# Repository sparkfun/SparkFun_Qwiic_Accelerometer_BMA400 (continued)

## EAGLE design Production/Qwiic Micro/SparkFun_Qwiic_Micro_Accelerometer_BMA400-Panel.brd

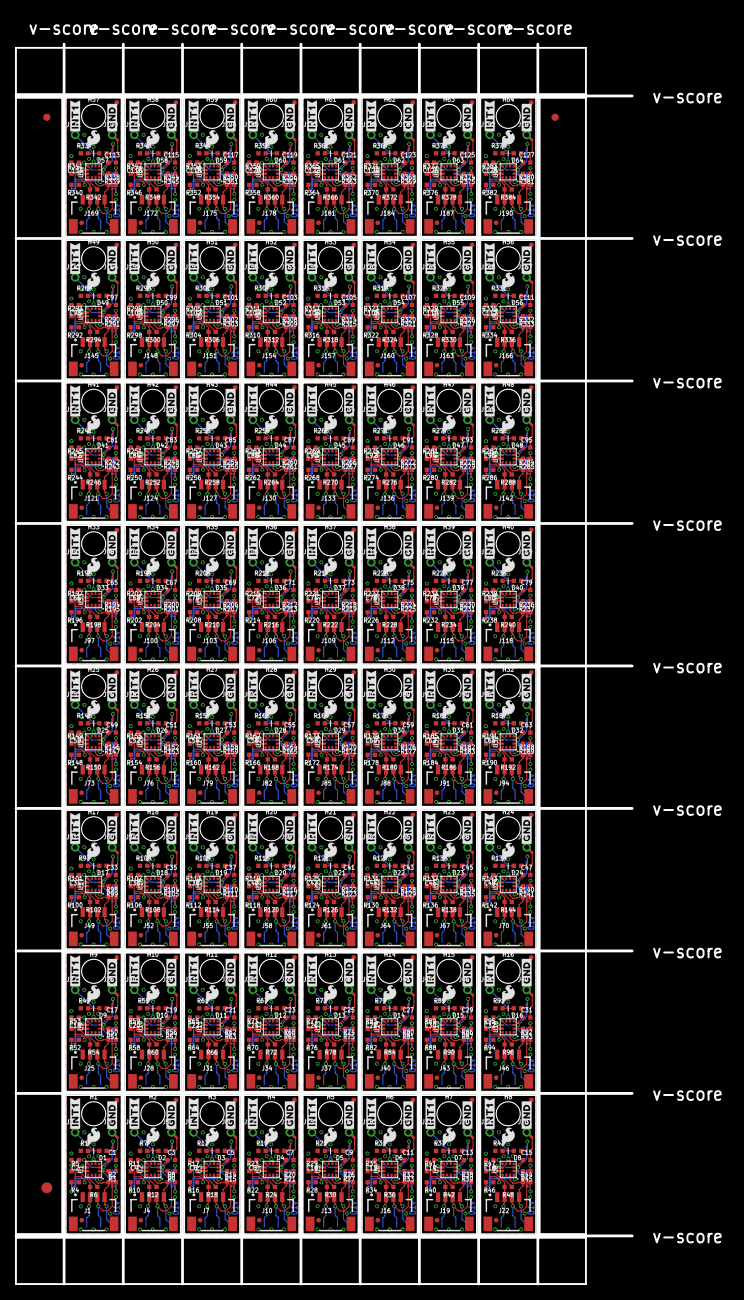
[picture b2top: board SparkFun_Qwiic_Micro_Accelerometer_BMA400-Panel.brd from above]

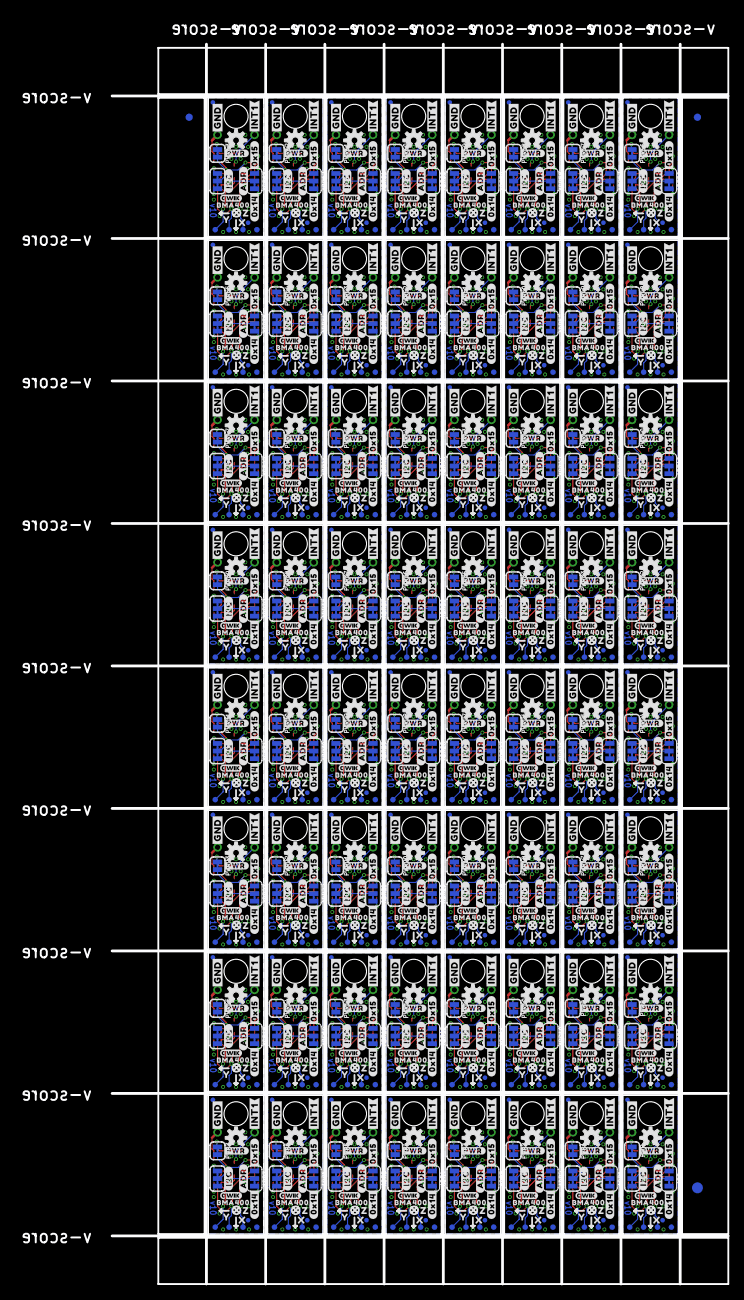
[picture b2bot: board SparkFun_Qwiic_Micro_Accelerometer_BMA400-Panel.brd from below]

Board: 2 copper layers, 84.6 x 170.2 mm, 2758 parts (1411 on the bottom side), 832 nets.

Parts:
ADR, ADR1, ADR2, ADR3, ADR4, ADR5, ADR6, ADR7, ADR8, ADR9, ADR10, ADR11, ADR12, ADR13, ADR14, ADR15, ADR16, ADR17, ADR18, ADR19, ADR20, ADR21, ADR22, ADR23, ADR24, ADR25, ADR26, ADR27, ADR28, ADR29, ADR30, ADR31, ADR32, ADR33, ADR34, ADR35, ADR36, ADR37, ADR38, ADR39, ADR40, ADR41, ADR42, ADR43, ADR44, ADR45, ADR46, ADR47, ADR48, ADR49, ADR50, ADR51, ADR52, ADR53, ADR54, ADR55, ADR56, ADR57, ADR58, ADR59, ADR60, ADR61, ADR62, ADR63: JUMPER-SMT_3_1-NC_TRACE_SILK; SMT-JUMPER_3_1-NC_TRACE_SILK
C1, C2, C3, C4, C5, C6, C7, C8, C9, C10, C11, C12, C13, C14, C15, C16, C17, C18, C19, C20, C21, C22, C23, C24, C25, C26, C27, C28, C29, C30, C31, C32, C33, C34, C35, C36, C37, C38, C39, C40, C41, C42, C43, C44, C45, C46, C47, C48, C49, C50, C51, C52, C53, C54, C55, C56, C57, C58, C59, C60, C61, C62, C63, C64, C65, C66, C67, C68, C69, C70, C71, C72, C73, C74, C75, C76, C77, C78, C79, C80, C81, C82, C83, C84, C85, C86, C87, C88, C89, C90, C91, C92, C93, C94, C95, C96, C97, C98, C99, C100, C101, C102, C103, C104, C105, C106, C107, C108, C109, C110, C111, C112, C113, C114, C115, C116, C117, C118, C119, C120, C121, C122, C123, C124, C125, C126, C127, C128: 0.1uF; 0402-TIGHT
D1, D2, D3, D4, D5, D6, D7, D8, D9, D10, D11, D12, D13, D14, D15, D16, D17, D18, D19, D20, D21, D22, D23, D24, D25, D26, D27, D28, D29, D30, D31, D32, D33, D34, D35, D36, D37, D38, D39, D40, D41, D42, D43, D44, D45, D46, D47, D48, D49, D50, D51, D52, D53, D54, D55, D56, D57, D58, D59, D60, D61, D62, D63, D64: RED; LED-0402
E$1, E$2, E$3, E$4: FIDUCIAL-1X2
E$5, E$6: FIDUCIAL-1.5X3
FD1, FD2, FD3, FD4, FD5, FD6, FD7, FD8, FD9, FD10, FD11, FD12, FD13, FD14, FD15, FD16, FD17, FD18, FD19, FD20, FD21, FD22, FD23, FD24, FD25, FD26, FD27, FD28, FD29, FD30, FD31, FD32, FD33, FD34, FD35, FD36, FD37, FD38, FD39, FD40, FD41, FD42, FD43, FD44, FD45, FD46, FD47, FD48, FD49, FD50, FD51, FD52, FD53, FD54, FD55, FD56, FD57, FD58, FD59, FD60, FD61, FD62, FD63, FD64, FD65, FD66, FD67, FD68, FD69, FD70, FD71, FD72, FD73, FD74, FD75, FD76, FD77, FD78, FD79, FD80, FD81, FD82, FD83, FD84, FD85, FD86, FD87, FD88, FD89, FD90, FD91, FD92, FD93, FD94, FD95, FD96, FD97, FD98, FD99, FD100, FD101, FD102, FD103, FD104, FD105, FD106, FD107, FD108, FD109, FD110, FD111, FD112, FD113, FD114, FD115, FD116, FD117, FD118, FD119, FD120, FD121, FD122, FD123, FD124, FD125, FD126, FD127, FD128, FD129, FD130, FD131, FD132, FD133, FD134, FD135, FD136, FD137, FD138, FD139, FD140, FD141, FD142, FD143, FD144, FD145, FD146, FD147, FD148, FD149, FD150, FD151, FD152, FD153, FD154, FD155, FD156, FD157, FD158, FD159, FD160, FD161, FD162, FD163, FD164, FD165, FD166, FD167, FD168, FD169, FD170, FD171, FD172, FD173, FD174, FD175, FD176, FD177, FD178, FD179, FD180, FD181, FD182, FD183, FD184, FD185, FD186, FD187, FD188, FD189, FD190, FD191, FD192, FD193, FD194, FD195, FD196, FD197, FD198, FD199, FD200, FD201, FD202, FD203, FD204, FD205, FD206, FD207, FD208, FD209, FD210, FD211, FD212, FD213, FD214, FD215, FD216, FD217, FD218, FD219, FD220, FD221, FD222, FD223, FD224, FD225, FD226, FD227, FD228, FD229, FD230, FD231, FD232, FD233, FD234, FD235, FD236, FD237, FD238, FD239, FD240, FD241, FD242, FD243, FD244, FD245, FD246, FD247, FD248, FD249, FD250, FD251, FD252, FD253, FD254, FD255, FD256: FIDUCIALUFIDUCIAL; FIDUCIAL-MICRO
FRAME1, FRAME2, FRAME3, FRAME4, FRAME5, FRAME6, FRAME7, FRAME8, FRAME9, FRAME10, FRAME11, FRAME12, FRAME13, FRAME14, FRAME15, FRAME16, FRAME17, FRAME18, FRAME19, FRAME20, FRAME21, FRAME22, FRAME23, FRAME24, FRAME25, FRAME26, FRAME27, FRAME28, FRAME29, FRAME30, FRAME31, FRAME32, FRAME33, FRAME34, FRAME35, FRAME36, FRAME37, FRAME38, FRAME39, FRAME40, FRAME41, FRAME42, FRAME43, FRAME44, FRAME45, FRAME46, FRAME47, FRAME48, FRAME49, FRAME50, FRAME51, FRAME52, FRAME53, FRAME54, FRAME55, FRAME56, FRAME57, FRAME58, FRAME59, FRAME60, FRAME61, FRAME62, FRAME63, FRAME64: FRAME-LETTER; CREATIVE_COMMONS
H1, H2, H3, H4, H5, H6, H7, H8, H9, H10, H11, H12, H13, H14, H15, H16, H17, H18, H19, H20, H21, H22, H23, H24, H25, H26, H27, H28, H29, H30, H31, H32, H33, H34, H35, H36, H37, H38, H39, H40, H41, H42, H43, H44, H45, H46, H47, H48, H49, H50, H51, H52, H53, H54, H55, H56, H57, H58, H59, H60, H61, H62, H63, H64: STAND-OFF
I2C, I2C1, I2C2, I2C3, I2C4, I2C5, I2C6, I2C7, I2C8, I2C9, I2C10, I2C11, I2C12, I2C13, I2C14, I2C15, I2C16, I2C17, I2C18, I2C19, I2C20, I2C21, I2C22, I2C23, I2C24, I2C25, I2C26, I2C27, I2C28, I2C29, I2C30, I2C31, I2C32, I2C33, I2C34, I2C35, I2C36, I2C37, I2C38, I2C39, I2C40, I2C41, I2C42, I2C43, I2C44, I2C45, I2C46, I2C47, I2C48, I2C49, I2C50, I2C51, I2C52, I2C53, I2C54, I2C55, I2C56, I2C57, I2C58, I2C59, I2C60, I2C61, I2C62, I2C63: JUMPER-SMT_3_2-NC_TRACE_SILK; SMT-JUMPER_3_2-NC_TRACE_SILK
J1, J4, J7, J10, J13, J16, J19, J22, J25, J28, J31, J34, J37, J40, J43, J46, J49, J52, J55, J58, J61, J64, J67, J70, J73, J76, J79, J82, J85, J88, J91, J94, J97, J100, J103, J106, J109, J112, J115, J118, J121, J124, J127, J130, J133, J136, J139, J142, J145, J148, J151, J154, J157, J160, J163, J166, J169, J172, J175, J178, J181, J184, J187, J190: QWIIC_RIGHT_ANGLE; JST04_1MM_RA
J2, J3, J5, J6, J8, J9, J11, J12, J14, J15, J17, J18, J20, J21, J23, J24, J26, J27, J29, J30, J32, J33, J35, J36, J38, J39, J41, J42, J44, J45, J47, J48, J50, J51, J53, J54, J56, J57, J59, J60, J62, J63, J65, J66, J68, J69, J71, J72, J74, J75, J77, J78, J80, J81, J83, J84, J86, J87, J89, J90, J92, J93, J95, J96, J98, J99, J101, J102, J104, J105, J107, J108, J110, J111, J113, J114, J116, J117, J119, J120, J122, J123, J125, J126, J128, J129, J131, J132, J134, J135, J137, J138, J140, J141, J143, J144, J146, J147, J149, J150, J152, J153, J155, J156, J158, J159, J161, J162, J164, J165, J167, J168, J170, J171, J173, J174, J176, J177, J179, J180, J182, J183, J185, J186, J188, J189, J191, J192: 1X01_1MM_NO_SILK
LOGO1, LOGO5, LOGO9, LOGO13, LOGO17, LOGO21, LOGO25, LOGO29, LOGO33, LOGO37, LOGO41, LOGO45, LOGO49, LOGO53, LOGO57, LOGO61, LOGO65, LOGO69, LOGO73, LOGO77, LOGO81, LOGO85, LOGO89, LOGO93, LOGO97, LOGO101, LOGO105, LOGO109, LOGO113, LOGO117, LOGO121, LOGO125, LOGO129, LOGO133, LOGO137, LOGO141, LOGO145, LOGO149, LOGO153, LOGO157, LOGO161, LOGO165, LOGO169, LOGO173, LOGO177, LOGO181, LOGO185, LOGO189, LOGO193, LOGO197, LOGO201, LOGO205, LOGO209, LOGO213, LOGO217, LOGO221, LOGO225, LOGO229, LOGO233, LOGO237, LOGO241, LOGO245, LOGO249, LOGO253: QWIIC_LOGO_3MM; QWIIC_3MM
LOGO2, LOGO6, LOGO10, LOGO14, LOGO18, LOGO22, LOGO26, LOGO30, LOGO34, LOGO38, LOGO42, LOGO46, LOGO50, LOGO54, LOGO58, LOGO62, LOGO66, LOGO70, LOGO74, LOGO78, LOGO82, LOGO86, LOGO90, LOGO94, LOGO98, LOGO102, LOGO106, LOGO110, LOGO114, LOGO118, LOGO122, LOGO126, LOGO130, LOGO134, LOGO138, LOGO142, LOGO146, LOGO150, LOGO154, LOGO158, LOGO162, LOGO166, LOGO170, LOGO174, LOGO178, LOGO182, LOGO186, LOGO190, LOGO194, LOGO198, LOGO202, LOGO206, LOGO210, LOGO214, LOGO218, LOGO222, LOGO226, LOGO230, LOGO234, LOGO238, LOGO242, LOGO246, LOGO250, LOGO254: SFE_LOGO_NAMEBLANK; BLANK
LOGO3, LOGO7, LOGO11, LOGO15, LOGO19, LOGO23, LOGO27, LOGO31, LOGO35, LOGO39, LOGO43, LOGO47, LOGO51, LOGO55, LOGO59, LOGO63, LOGO67, LOGO71, LOGO75, LOGO79, LOGO83, LOGO87, LOGO91, LOGO95, LOGO99, LOGO103, LOGO107, LOGO111, LOGO115, LOGO119, LOGO123, LOGO127, LOGO131, LOGO135, LOGO139, LOGO143, LOGO147, LOGO151, LOGO155, LOGO159, LOGO163, LOGO167, LOGO171, LOGO175, LOGO179, LOGO183, LOGO187, LOGO191, LOGO195, LOGO199, LOGO203, LOGO207, LOGO211, LOGO215, LOGO219, LOGO223, LOGO227, LOGO231, LOGO235, LOGO239, LOGO243, LOGO247, LOGO251, LOGO255: OSHW-LOGOS; OSHW-LOGO-S
LOGO4, LOGO8, LOGO12, LOGO16, LOGO20, LOGO24, LOGO28, LOGO32, LOGO36, LOGO40, LOGO44, LOGO48, LOGO52, LOGO56, LOGO60, LOGO64, LOGO68, LOGO72, LOGO76, LOGO80, LOGO84, LOGO88, LOGO92, LOGO96, LOGO100, LOGO104, LOGO108, LOGO112, LOGO116, LOGO120, LOGO124, LOGO128, LOGO132, LOGO136, LOGO140, LOGO144, LOGO148, LOGO152, LOGO156, LOGO160, LOGO164, LOGO168, LOGO172, LOGO176, LOGO180, LOGO184, LOGO188, LOGO192, LOGO196, LOGO200, LOGO204, LOGO208, LOGO212, LOGO216, LOGO220, LOGO224, LOGO228, LOGO232, LOGO236, LOGO240, LOGO244, LOGO248, LOGO252, LOGO256: SFE_LOGO_FLAME.1_INCH; SFE_LOGO_FLAME_.1
PWR, PWR1, PWR2, PWR3, PWR4, PWR5, PWR6, PWR7, PWR8, PWR9, PWR10, PWR11, PWR12, PWR13, PWR14, PWR15, PWR16, PWR17, PWR18, PWR19, PWR20, PWR21, PWR22, PWR23, PWR24, PWR25, PWR26, PWR27, PWR28, PWR29, PWR30, PWR31, PWR32, PWR33, PWR34, PWR35, PWR36, PWR37, PWR38, PWR39, PWR40, PWR41, PWR42, PWR43, PWR44, PWR45, PWR46, PWR47, PWR48, PWR49, PWR50, PWR51, PWR52, PWR53, PWR54, PWR55, PWR56, PWR57, PWR58, PWR59, PWR60, PWR61, PWR62, PWR63: JUMPER-SMT_2_NC_TRACE_SILK; SMT-JUMPER_2_NC_TRACE_SILK
R1, R2, R3, R7, R8, R9, R13, R14, R15, R19, R20, R21, R25, R26, R27, R31, R32, R33, R37, R38, R39, R43, R44, R45, R49, R50, R51, R55, R56, R57, R61, R62, R63, R67, R68, R69, R73, R74, R75, R79, R80, R81, R85, R86, R87, R91, R92, R93, R97, R98, R99, R103, R104, R105, R109, R110, R111, R115, R116, R117, R121, R122, R123, R127, R128, R129, R133, R134, R135, R139, R140, R141, R145, R146, R147, R151, R152, R153, R157, R158, R159, R163, R164, R165, R169, R170, R171, R175, R176, R177, R181, R182, R183, R187, R188, R189, R193, R194, R195, R199, R200, R201, R205, R206, R207, R211, R212, R213, R217, R218, R219, R223, R224, R225, R229, R230, R231, R235, R236, R237, R241, R242, R243, R247, R248, R249, R253, R254, R255, R259, R260, R261, R265, R266, R267, R271, R272, R273, R277, R278, R279, R283, R284, R285, R289, R290, R291, R295, R296, R297, R301, R302, R303, R307, R308, R309, R313, R314, R315, R319, R320, R321, R325, R326, R327, R331, R332, R333, R337, R338, R339, R343, R344, R345, R349, R350, R351, R355, R356, R357, R361, R362, R363, R367, R368, R369, R373, R374, R375, R379, R380, R381: 2.2k; 0402-TIGHT
R4, R5, R6, R10, R11, R12, R16, R17, R18, R22, R23, R24, R28, R29, R30, R34, R35, R36, R40, R41, R42, R46, R47, R48, R52, R53, R54, R58, R59, R60, R64, R65, R66, R70, R71, R72, R76, R77, R78, R82, R83, R84, R88, R89, R90, R94, R95, R96, R100, R101, R102, R106, R107, R108, R112, R113, R114, R118, R119, R120, R124, R125, R126, R130, R131, R132, R136, R137, R138, R142, R143, R144, R148, R149, R150, R154, R155, R156, R160, R161, R162, R166, R167, R168, R172, R173, R174, R178, R179, R180, R184, R185, R186, R190, R191, R192, R196, R197, R198, R202, R203, R204, R208, R209, R210, R214, R215, R216, R220, R221, R222, R226, R227, R228, R232, R233, R234, R238, R239, R240, R244, R245, R246, R250, R251, R252, R256, R257, R258, R262, R263, R264, R268, R269, R270, R274, R275, R276, R280, R281, R282, R286, R287, R288, R292, R293, R294, R298, R299, R300, R304, R305, R306, R310, R311, R312, R316, R317, R318, R322, R323, R324, R328, R329, R330, R334, R335, R336, R340, R341, R342, R346, R347, R348, R352, R353, R354, R358, R359, R360, R364, R365, R366, R370, R371, R372, R376, R377, R378, R382, R383, R384: 10k; 0402-TIGHT
TP1, TP2, TP3, TP4, TP5, TP6, TP7, TP8, TP9, TP10, TP11, TP12, TP13, TP14, TP15, TP16, TP17, TP18, TP19, TP20, TP21, TP22, TP23, TP24, TP25, TP26, TP27, TP28, TP29, TP30, TP31, TP32, TP33, TP34, TP35, TP36, TP37, TP38, TP39, TP40, TP41, TP42, TP43, TP44, TP45, TP46, TP47, TP48, TP49, TP50, TP51, TP52, TP53, TP54, TP55, TP56, TP57, TP58, TP59, TP60, TP61, TP62, TP63, TP64, TP65, TP66, TP67, TP68, TP69, TP70, TP71, TP72, TP73, TP74, TP75, TP76, TP77, TP78, TP79, TP80, TP81, TP82, TP83, TP84, TP85, TP86, TP87, TP88, TP89, TP90, TP91, TP92, TP93, TP94, TP95, TP96, TP97, TP98, TP99, TP100, TP101, TP102, TP103, TP104, TP105, TP106, TP107, TP108, TP109, TP110, TP111, TP112, TP113, TP114, TP115, TP116, TP117, TP118, TP119, TP120, TP121, TP122, TP123, TP124, TP125, TP126, TP127, TP128, TP129, TP130, TP131, TP132, TP133, TP134, TP135, TP136, TP137, TP138, TP139, TP140, TP141, TP142, TP143, TP144, TP145, TP146, TP147, TP148, TP149, TP150, TP151, TP152, TP153, TP154, TP155, TP156, TP157, TP158, TP159, TP160, TP161, TP162, TP163, TP164, TP165, TP166, TP167, TP168, TP169, TP170, TP171, TP172, TP173, TP174, TP175, TP176, TP177, TP178, TP179, TP180, TP181, TP182, TP183, TP184, TP185, TP186, TP187, TP188, TP189, TP190, TP191, TP192, TP193, TP194, TP195, TP196, TP197, TP198, TP199, TP200, TP201, TP202, TP203, TP204, TP205, TP206, TP207, TP208, TP209, TP210, TP211, TP212, TP213, TP214, TP215, TP216, TP217, TP218, TP219, TP220, TP221, TP222, TP223, TP224, TP225, TP226, TP227, TP228, TP229, TP230, TP231, TP232, TP233, TP234, TP235, TP236, TP237, TP238, TP239, TP240, TP241, TP242, TP243, TP244, TP245, TP246, TP247, TP248, TP249, TP250, TP251, TP252, TP253, TP254, TP255, TP256: TEST-POINT3; PAD.03X.03
U1, U2, U3, U4, U5, U6, U7, U8, U9, U10, U11, U12, U13, U14, U15, U16, U17, U18, U19, U20, U21, U22, U23, U24, U25, U26, U27, U28, U29, U30, U31, U32, U33, U34, U35, U36, U37, U38, U39, U40, U41, U42, U43, U44, U45, U46, U47, U48, U49, U50, U51, U52, U53, U54, U55, U56, U57, U58, U59, U60, U61, U62, U63, U64: BMA400
U$1, U$4, U$14, U$17, U$27, U$30, U$40, U$43, U$53, U$56, U$66, U$69, U$79, U$82, U$92, U$95, U$105, U$108, U$118, U$121, U$131, U$134, U$144, U$147, U$157, U$160, U$170, U$173, U$183, U$186, U$196, U$199, U$209, U$212, U$222, U$225, U$235, U$238, U$248, U$251, U$261, U$264, U$274, U$277, U$287, U$290, U$300, U$303, U$313, U$316, U$326, U$329, U$339, U$342, U$352, U$355, U$365, U$368, U$378, U$381, U$391, U$394, U$404, U$407, U$417, U$420, U$430, U$433, U$443, U$446, U$456, U$459, U$469, U$472, U$482, U$485, U$495, U$498, U$508, U$511, U$521, U$524, U$534, U$537, U$547, U$550, U$560, U$563, U$573, U$576, U$586, U$589, U$599, U$602, U$612, U$615, U$625, U$628, U$638, U$641, U$651, U$654, U$664, U$667, U$677, U$680, U$690, U$693, U$703, U$706, U$716, U$719, U$729, U$732, U$742, U$745, U$755, U$758, U$768, U$771, U$781, U$784, U$794, U$797, U$807, U$810, U$820, U$823: #INT1#0
U$2, U$3, U$15, U$16, U$28, U$29, U$41, U$42, U$54, U$55, U$67, U$68, U$80, U$81, U$93, U$94, U$106, U$107, U$119, U$120, U$132, U$133, U$145, U$146, U$158, U$159, U$171, U$172, U$184, U$185, U$197, U$198, U$210, U$211, U$223, U$224, U$236, U$237, U$249, U$250, U$262, U$263, U$275, U$276, U$288, U$289, U$301, U$302, U$314, U$315, U$327, U$328, U$340, U$341, U$353, U$354, U$366, U$367, U$379, U$380, U$392, U$393, U$405, U$406, U$418, U$419, U$431, U$432, U$444, U$445, U$457, U$458, U$470, U$471, U$483, U$484, U$496, U$497, U$509, U$510, U$522, U$523, U$535, U$536, U$548, U$549, U$561, U$562, U$574, U$575, U$587, U$588, U$600, U$601, U$613, U$614, U$626, U$627, U$639, U$640, U$652, U$653, U$665, U$666, U$678, U$679, U$691, U$692, U$704, U$705, U$717, U$718, U$730, U$731, U$743, U$744, U$756, U$757, U$769, U$770, U$782, U$783, U$795, U$796, U$808, U$809, U$821, U$822: #GND#0
U$5, U$18, U$31, U$44, U$57, U$70, U$83, U$96, U$109, U$122, U$135, U$148, U$161, U$174, U$187, U$200, U$213, U$226, U$239, U$252, U$265, U$278, U$291, U$304, U$317, U$330, U$343, U$356, U$369, U$382, U$395, U$408, U$421, U$434, U$447, U$460, U$473, U$486, U$499, U$512, U$525, U$538, U$551, U$564, U$577, U$590, U$603, U$616, U$629, U$642, U$655, U$668, U$681, U$694, U$707, U$720, U$733, U$746, U$759, U$772, U$785, U$798, U$811, U$824: BMA4000
U$6, U$24, U$37, U$50, U$63, U$76, U$89, U$102, U$115, U$128, U$141, U$154, U$167, U$180, U$193, U$206, U$219, U$232, U$245, U$258, U$271, U$284, U$297, U$310, U$323, U$336, U$349, U$362, U$375, U$388, U$401, U$414, U$427, U$440, U$453, U$466, U$479, U$492, U$505, U$518, U$531, U$544, U$557, U$570, U$583, U$596, U$609, U$622, U$635, U$648, U$661, U$674, U$687, U$700, U$713, U$726, U$739, U$752, U$765, U$778, U$791, U$804, U$817, U$830: X2114
U$7, U$19, U$32, U$45, U$58, U$71, U$84, U$97, U$110, U$123, U$136, U$149, U$162, U$175, U$188, U$201, U$214, U$227, U$240, U$253, U$266, U$279, U$292, U$305, U$318, U$331, U$344, U$357, U$370, U$383, U$396, U$409, U$422, U$435, U$448, U$461, U$474, U$487, U$500, U$513, U$526, U$539, U$552, U$565, U$578, U$591, U$604, U$617, U$630, U$643, U$656, U$669, U$682, U$695, U$708, U$721, U$734, U$747, U$760, U$773, U$786, U$799, U$812, U$825: #I2C#0
U$8, U$20, U$33, U$46, U$59, U$72, U$85, U$98, U$111, U$124, U$137, U$150, U$163, U$176, U$189, U$202, U$215, U$228, U$241, U$254, U$267, U$280, U$293, U$306, U$319, U$332, U$345, U$358, U$371, U$384, U$397, U$410, U$423, U$436, U$449, U$462, U$475, U$488, U$501, U$514, U$527, U$540, U$553, U$566, U$579, U$592, U$605, U$618, U$631, U$644, U$657, U$670, U$683, U$696, U$709, U$722, U$735, U$748, U$761, U$774, U$787, U$800, U$813, U$826: #ADR#0
U$9, U$21, U$34, U$47, U$60, U$73, U$86, U$99, U$112, U$125, U$138, U$151, U$164, U$177, U$190, U$203, U$216, U$229, U$242, U$255, U$268, U$281, U$294, U$307, U$320, U$333, U$346, U$359, U$372, U$385, U$398, U$411, U$424, U$437, U$450, U$463, U$476, U$489, U$502, U$515, U$528, U$541, U$554, U$567, U$580, U$593, U$606, U$619, U$632, U$645, U$658, U$671, U$684, U$697, U$710, U$723, U$736, U$749, U$762, U$775, U$788, U$801, U$814, U$827: #0X15#0
U$10, U$22, U$35, U$48, U$61, U$74, U$87, U$100, U$113, U$126, U$139, U$152, U$165, U$178, U$191, U$204, U$217, U$230, U$243, U$256, U$269, U$282, U$295, U$308, U$321, U$334, U$347, U$360, U$373, U$386, U$399, U$412, U$425, U$438, U$451, U$464, U$477, U$490, U$503, U$516, U$529, U$542, U$555, U$568, U$581, U$594, U$607, U$620, U$633, U$646, U$659, U$672, U$685, U$698, U$711, U$724, U$737, U$750, U$763, U$776, U$789, U$802, U$815, U$828: #0X14#0
U$11, U$23, U$36, U$49, U$62, U$75, U$88, U$101, U$114, U$127, U$140, U$153, U$166, U$179, U$192, U$205, U$218, U$231, U$244, U$257, U$270, U$283, U$296, U$309, U$322, U$335, U$348, U$361, U$374, U$387, U$400, U$413, U$426, U$439, U$452, U$465, U$478, U$491, U$504, U$517, U$530, U$543, U$556, U$569, U$582, U$595, U$608, U$621, U$634, U$647, U$660, U$673, U$686, U$699, U$712, U$725, U$738, U$751, U$764, U$777, U$790, U$803, U$816, U$829: #PWR#0
U$12, U$25, U$38, U$51, U$64, U$77, U$90, U$103, U$116, U$129, U$142, U$155, U$168, U$181, U$194, U$207, U$220, U$233, U$246, U$259, U$272, U$285, U$298, U$311, U$324, U$337, U$350, U$363, U$376, U$389, U$402, U$415, U$428, U$441, U$454, U$467, U$480, U$493, U$506, U$519, U$532, U$545, U$558, U$571, U$584, U$597, U$610, U$623, U$636, U$649, U$662, U$675, U$688, U$701, U$714, U$727, U$740, U$753, U$766, U$779, U$792, U$805, U$818, U$831: Y2115
U$13, U$26, U$39, U$52, U$65, U$78, U$91, U$104, U$117, U$130, U$143, U$156, U$169, U$182, U$195, U$208, U$221, U$234, U$247, U$260, U$273, U$286, U$299, U$312, U$325, U$338, U$351, U$364, U$377, U$390, U$403, U$416, U$429, U$442, U$455, U$468, U$481, U$494, U$507, U$520, U$533, U$546, U$559, U$572, U$585, U$598, U$611, U$624, U$637, U$650, U$663, U$676, U$689, U$702, U$715, U$728, U$741, U$754, U$767, U$780, U$793, U$806, U$819, U$832: Z2116

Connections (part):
3.3V: C1.1, C2.1, I2C.2, J1.2, PWR.2, R5.2, R6.2, TP2.1, U1.3, U1.7
3.3V1: C3.1, C4.1, I2C1.2, J4.2, PWR1.2, R11.2, R12.2, TP6.1, U2.3, U2.7
3.3V2: C5.1, C6.1, I2C2.2, J7.2, PWR2.2, R17.2, R18.2, TP10.1, U3.3, U3.7
3.3V3: C7.1, C8.1, I2C3.2, J10.2, PWR3.2, R23.2, R24.2, TP14.1, U4.3, U4.7
3.3V4: C9.1, C10.1, I2C4.2, J13.2, PWR4.2, R29.2, R30.2, TP18.1, U5.3, U5.7
3.3V5: C11.1, C12.1, I2C5.2, J16.2, PWR5.2, R35.2, R36.2, TP22.1, U6.3, U6.7
3.3V6: C13.1, C14.1, I2C6.2, J19.2, PWR6.2, R41.2, R42.2, TP26.1, U7.3, U7.7
3.3V7: C15.1, C16.1, I2C7.2, J22.2, PWR7.2, R47.2, R48.2, TP30.1, U8.3, U8.7
3.3V8: C17.1, C18.1, I2C8.2, J25.2, PWR8.2, R53.2, R54.2, TP34.1, U9.3, U9.7
3.3V9: C19.1, C20.1, I2C9.2, J28.2, PWR9.2, R59.2, R60.2, TP38.1, U10.3, U10.7
3.3V10: C21.1, C22.1, I2C10.2, J31.2, PWR10.2, R65.2, R66.2, TP42.1, U11.3, U11.7
3.3V11: C23.1, C24.1, I2C11.2, J34.2, PWR11.2, R71.2, R72.2, TP46.1, U12.3, U12.7
3.3V12: C25.1, C26.1, I2C12.2, J37.2, PWR12.2, R77.2, R78.2, TP50.1, U13.3, U13.7
3.3V13: C27.1, C28.1, I2C13.2, J40.2, PWR13.2, R83.2, R84.2, TP54.1, U14.3, U14.7
3.3V14: C29.1, C30.1, I2C14.2, J43.2, PWR14.2, R89.2, R90.2, TP58.1, U15.3, U15.7
3.3V15: C31.1, C32.1, I2C15.2, J46.2, PWR15.2, R95.2, R96.2, TP62.1, U16.3, U16.7
3.3V16: C33.1, C34.1, I2C16.2, J49.2, PWR16.2, R101.2, R102.2, TP66.1, U17.3, U17.7
3.3V17: C35.1, C36.1, I2C17.2, J52.2, PWR17.2, R107.2, R108.2, TP70.1, U18.3, U18.7
3.3V18: C37.1, C38.1, I2C18.2, J55.2, PWR18.2, R113.2, R114.2, TP74.1, U19.3, U19.7
3.3V19: C39.1, C40.1, I2C19.2, J58.2, PWR19.2, R119.2, R120.2, TP78.1, U20.3, U20.7
3.3V20: C41.1, C42.1, I2C20.2, J61.2, PWR20.2, R125.2, R126.2, TP82.1, U21.3, U21.7
3.3V21: C43.1, C44.1, I2C21.2, J64.2, PWR21.2, R131.2, R132.2, TP86.1, U22.3, U22.7
3.3V22: C45.1, C46.1, I2C22.2, J67.2, PWR22.2, R137.2, R138.2, TP90.1, U23.3, U23.7
3.3V23: C47.1, C48.1, I2C23.2, J70.2, PWR23.2, R143.2, R144.2, TP94.1, U24.3, U24.7
3.3V24: C49.1, C50.1, I2C24.2, J73.2, PWR24.2, R149.2, R150.2, TP98.1, U25.3, U25.7
3.3V25: C51.1, C52.1, I2C25.2, J76.2, PWR25.2, R155.2, R156.2, TP102.1, U26.3, U26.7
3.3V26: C53.1, C54.1, I2C26.2, J79.2, PWR26.2, R161.2, R162.2, TP106.1, U27.3, U27.7
3.3V27: C55.1, C56.1, I2C27.2, J82.2, PWR27.2, R167.2, R168.2, TP110.1, U28.3, U28.7
3.3V28: C57.1, C58.1, I2C28.2, J85.2, PWR28.2, R173.2, R174.2, TP114.1, U29.3, U29.7
3.3V29: C59.1, C60.1, I2C29.2, J88.2, PWR29.2, R179.2, R180.2, TP118.1, U30.3, U30.7
3.3V30: C61.1, C62.1, I2C30.2, J91.2, PWR30.2, R185.2, R186.2, TP122.1, U31.3, U31.7
3.3V31: C63.1, C64.1, I2C31.2, J94.2, PWR31.2, R191.2, R192.2, TP126.1, U32.3, U32.7
3.3V32: C65.1, C66.1, I2C32.2, J97.2, PWR32.2, R197.2, R198.2, TP130.1, U33.3, U33.7
3.3V33: C67.1, C68.1, I2C33.2, J100.2, PWR33.2, R203.2, R204.2, TP134.1, U34.3, U34.7
3.3V34: C69.1, C70.1, I2C34.2, J103.2, PWR34.2, R209.2, R210.2, TP138.1, U35.3, U35.7
3.3V35: C71.1, C72.1, I2C35.2, J106.2, PWR35.2, R215.2, R216.2, TP142.1, U36.3, U36.7
3.3V36: C73.1, C74.1, I2C36.2, J109.2, PWR36.2, R221.2, R222.2, TP146.1, U37.3, U37.7
3.3V37: C75.1, C76.1, I2C37.2, J112.2, PWR37.2, R227.2, R228.2, TP150.1, U38.3, U38.7
3.3V38: C77.1, C78.1, I2C38.2, J115.2, PWR38.2, R233.2, R234.2, TP154.1, U39.3, U39.7
3.3V39: C79.1, C80.1, I2C39.2, J118.2, PWR39.2, R239.2, R240.2, TP158.1, U40.3, U40.7
3.3V40: C81.1, C82.1, I2C40.2, J121.2, PWR40.2, R245.2, R246.2, TP162.1, U41.3, U41.7
3.3V41: C83.1, C84.1, I2C41.2, J124.2, PWR41.2, R251.2, R252.2, TP166.1, U42.3, U42.7
3.3V42: C85.1, C86.1, I2C42.2, J127.2, PWR42.2, R257.2, R258.2, TP170.1, U43.3, U43.7
3.3V43: C87.1, C88.1, I2C43.2, J130.2, PWR43.2, R263.2, R264.2, TP174.1, U44.3, U44.7
3.3V44: C89.1, C90.1, I2C44.2, J133.2, PWR44.2, R269.2, R270.2, TP178.1, U45.3, U45.7
3.3V45: C91.1, C92.1, I2C45.2, J136.2, PWR45.2, R275.2, R276.2, TP182.1, U46.3, U46.7
3.3V46: C93.1, C94.1, I2C46.2, J139.2, PWR46.2, R281.2, R282.2, TP186.1, U47.3, U47.7
3.3V47: C95.1, C96.1, I2C47.2, J142.2, PWR47.2, R287.2, R288.2, TP190.1, U48.3, U48.7
3.3V48: C97.1, C98.1, I2C48.2, J145.2, PWR48.2, R293.2, R294.2, TP194.1, U49.3, U49.7
3.3V49: C99.1, C100.1, I2C49.2, J148.2, PWR49.2, R299.2, R300.2, TP198.1, U50.3, U50.7
3.3V50: C101.1, C102.1, I2C50.2, J151.2, PWR50.2, R305.2, R306.2, TP202.1, U51.3, U51.7
3.3V51: C103.1, C104.1, I2C51.2, J154.2, PWR51.2, R311.2, R312.2, TP206.1, U52.3, U52.7
3.3V52: C105.1, C106.1, I2C52.2, J157.2, PWR52.2, R317.2, R318.2, TP210.1, U53.3, U53.7
3.3V53: C107.1, C108.1, I2C53.2, J160.2, PWR53.2, R323.2, R324.2, TP214.1, U54.3, U54.7
3.3V54: C109.1, C110.1, I2C54.2, J163.2, PWR54.2, R329.2, R330.2, TP218.1, U55.3, U55.7
3.3V55: C111.1, C112.1, I2C55.2, J166.2, PWR55.2, R335.2, R336.2, TP222.1, U56.3, U56.7
3.3V56: C113.1, C114.1, I2C56.2, J169.2, PWR56.2, R341.2, R342.2, TP226.1, U57.3, U57.7
3.3V57: C115.1, C116.1, I2C57.2, J172.2, PWR57.2, R347.2, R348.2, TP230.1, U58.3, U58.7
3.3V58: C117.1, C118.1, I2C58.2, J175.2, PWR58.2, R353.2, R354.2, TP234.1, U59.3, U59.7
3.3V59: C119.1, C120.1, I2C59.2, J178.2, PWR59.2, R359.2, R360.2, TP238.1, U60.3, U60.7
3.3V60: C121.1, C122.1, I2C60.2, J181.2, PWR60.2, R365.2, R366.2, TP242.1, U61.3, U61.7
3.3V61: C123.1, C124.1, I2C61.2, J184.2, PWR61.2, R371.2, R372.2, TP246.1, U62.3, U62.7
3.3V62: C125.1, C126.1, I2C62.2, J187.2, PWR62.2, R377.2, R378.2, TP250.1, U63.3, U63.7
3.3V63: C127.1, C128.1, I2C63.2, J190.2, PWR63.2, R383.2, R384.2, TP254.1, U64.3, U64.7
!CS!: R6.1, U1.10
!CS!1: R12.1, U2.10
!CS!2: R18.1, U3.10
!CS!3: R24.1, U4.10
!CS!4: R30.1, U5.10
!CS!5: R36.1, U6.10
!CS!6: R42.1, U7.10
!CS!7: R48.1, U8.10
!CS!8: R54.1, U9.10
!CS!9: R60.1, U10.10
!CS!10: R66.1, U11.10
!CS!11: R72.1, U12.10
!CS!12: R78.1, U13.10
!CS!13: R84.1, U14.10
!CS!14: R90.1, U15.10
!CS!15: R96.1, U16.10
!CS!16: R102.1, U17.10
!CS!17: R108.1, U18.10
!CS!18: R114.1, U19.10
!CS!19: R120.1, U20.10
!CS!20: R126.1, U21.10
!CS!21: R132.1, U22.10
!CS!22: R138.1, U23.10
!CS!23: R144.1, U24.10
!CS!24: R150.1, U25.10
!CS!25: R156.1, U26.10
!CS!26: R162.1, U27.10
!CS!27: R168.1, U28.10
!CS!28: R174.1, U29.10
!CS!29: R180.1, U30.10
!CS!30: R186.1, U31.10
!CS!31: R192.1, U32.10
!CS!32: R198.1, U33.10
!CS!33: R204.1, U34.10
!CS!34: R210.1, U35.10
!CS!35: R216.1, U36.10
!CS!36: R222.1, U37.10
!CS!37: R228.1, U38.10
!CS!38: R234.1, U39.10
!CS!39: R240.1, U40.10
!CS!40: R246.1, U41.10
!CS!41: R252.1, U42.10
!CS!42: R258.1, U43.10
!CS!43: R264.1, U44.10
!CS!44: R270.1, U45.10
!CS!45: R276.1, U46.10
!CS!46: R282.1, U47.10
!CS!47: R288.1, U48.10
!CS!48: R294.1, U49.10
!CS!49: R300.1, U50.10
!CS!50: R306.1, U51.10
!CS!51: R312.1, U52.10
!CS!52: R318.1, U53.10
!CS!53: R324.1, U54.10
!CS!54: R330.1, U55.10
!CS!55: R336.1, U56.10
!CS!56: R342.1, U57.10
!CS!57: R348.1, U58.10
!CS!58: R354.1, U59.10
!CS!59: R360.1, U60.10
!CS!60: R366.1, U61.10
!CS!61: R372.1, U62.10
!CS!62: R378.1, U63.10
!CS!63: R384.1, U64.10
ADR: ADR.2, U1.1
ADR1: ADR1.2, U2.1
ADR2: ADR2.2, U3.1
ADR3: ADR3.2, U4.1
ADR4: ADR4.2, U5.1
ADR5: ADR5.2, U6.1
ADR6: ADR6.2, U7.1
ADR7: ADR7.2, U8.1
ADR8: ADR8.2, U9.1
ADR9: ADR9.2, U10.1
ADR10: ADR10.2, U11.1
ADR11: ADR11.2, U12.1
ADR12: ADR12.2, U13.1
ADR13: ADR13.2, U14.1
ADR14: ADR14.2, U15.1
ADR15: ADR15.2, U16.1
ADR16: ADR16.2, U17.1
ADR17: ADR17.2, U18.1
ADR18: ADR18.2, U19.1
ADR19: ADR19.2, U20.1
ADR20: ADR20.2, U21.1
ADR21: ADR21.2, U22.1
ADR22: ADR22.2, U23.1
ADR23: ADR23.2, U24.1
ADR24: ADR24.2, U25.1
ADR25: ADR25.2, U26.1
ADR26: ADR26.2, U27.1
ADR27: ADR27.2, U28.1
ADR28: ADR28.2, U29.1
ADR29: ADR29.2, U30.1
ADR30: ADR30.2, U31.1
ADR31: ADR31.2, U32.1
ADR32: ADR32.2, U33.1
ADR33: ADR33.2, U34.1
ADR34: ADR34.2, U35.1
ADR35: ADR35.2, U36.1
ADR36: ADR36.2, U37.1
ADR37: ADR37.2, U38.1
ADR38: ADR38.2, U39.1
ADR39: ADR39.2, U40.1
ADR40: ADR40.2, U41.1
ADR41: ADR41.2, U42.1
ADR42: ADR42.2, U43.1
ADR43: ADR43.2, U44.1
ADR44: ADR44.2, U45.1
ADR45: ADR45.2, U46.1
ADR46: ADR46.2, U47.1
ADR47: ADR47.2, U48.1
ADR48: ADR48.2, U49.1
ADR49: ADR49.2, U50.1
ADR50: ADR50.2, U51.1
ADR51: ADR51.2, U52.1
ADR52: ADR52.2, U53.1
ADR53: ADR53.2, U54.1
ADR54: ADR54.2, U55.1
ADR55: ADR55.2, U56.1
ADR56: ADR56.2, U57.1
ADR57: ADR57.2, U58.1
ADR58: ADR58.2, U59.1
ADR59: ADR59.2, U60.1
ADR60: ADR60.2, U61.1
ADR61: ADR61.2, U62.1
ADR62: ADR62.2, U63.1
ADR63: ADR63.2, U64.1
GND: C1.2, C2.2, J1.1, J2.1, R1.1, R4.1, TP1.1, U1.8, U1.9
GND1: C3.2, C4.2, J4.1, J5.1, R7.1, R10.1, TP5.1, U2.8, U2.9
GND2: C5.2, C6.2, J7.1, J8.1, R13.1, R16.1, TP9.1, U3.8, U3.9
GND3: C7.2, C8.2, J10.1, J11.1, R19.1, R22.1, TP13.1, U4.8, U4.9
GND4: C9.2, C10.2, J13.1, J14.1, R25.1, R28.1, TP17.1, U5.8, U5.9
GND5: C11.2, C12.2, J16.1, J17.1, R31.1, R34.1, TP21.1, U6.8, U6.9
GND6: C13.2, C14.2, J19.1, J20.1, R37.1, R40.1, TP25.1, U7.8, U7.9
GND7: C15.2, C16.2, J22.1, J23.1, R43.1, R46.1, TP29.1, U8.8, U8.9
GND8: C17.2, C18.2, J25.1, J26.1, R49.1, R52.1, TP33.1, U9.8, U9.9
GND9: C19.2, C20.2, J28.1, J29.1, R55.1, R58.1, TP37.1, U10.8, U10.9
GND10: C21.2, C22.2, J31.1, J32.1, R61.1, R64.1, TP41.1, U11.8, U11.9
GND11: C23.2, C24.2, J34.1, J35.1, R67.1, R70.1, TP45.1, U12.8, U12.9
GND12: C25.2, C26.2, J37.1, J38.1, R73.1, R76.1, TP49.1, U13.8, U13.9
GND13: C27.2, C28.2, J40.1, J41.1, R79.1, R82.1, TP53.1, U14.8, U14.9
GND14: C29.2, C30.2, J43.1, J44.1, R85.1, R88.1, TP57.1, U15.8, U15.9
GND15: C31.2, C32.2, J46.1, J47.1, R91.1, R94.1, TP61.1, U16.8, U16.9
GND16: C33.2, C34.2, J49.1, J50.1, R97.1, R100.1, TP65.1, U17.8, U17.9
GND17: C35.2, C36.2, J52.1, J53.1, R103.1, R106.1, TP69.1, U18.8, U18.9
GND18: C37.2, C38.2, J55.1, J56.1, R109.1, R112.1, TP73.1, U19.8, U19.9
GND19: C39.2, C40.2, J58.1, J59.1, R115.1, R118.1, TP77.1, U20.8, U20.9
GND20: C41.2, C42.2, J61.1, J62.1, R121.1, R124.1, TP81.1, U21.8, U21.9
GND21: C43.2, C44.2, J64.1, J65.1, R127.1, R130.1, TP85.1, U22.8, U22.9
GND22: C45.2, C46.2, J67.1, J68.1, R133.1, R136.1, TP89.1, U23.8, U23.9
GND23: C47.2, C48.2, J70.1, J71.1, R139.1, R142.1, TP93.1, U24.8, U24.9
GND24: C49.2, C50.2, J73.1, J74.1, R145.1, R148.1, TP97.1, U25.8, U25.9
GND25: C51.2, C52.2, J76.1, J77.1, R151.1, R154.1, TP101.1, U26.8, U26.9
GND26: C53.2, C54.2, J79.1, J80.1, R157.1, R160.1, TP105.1, U27.8, U27.9
GND27: C55.2, C56.2, J82.1, J83.1, R163.1, R166.1, TP109.1, U28.8, U28.9
GND28: C57.2, C58.2, J85.1, J86.1, R169.1, R172.1, TP113.1, U29.8, U29.9
GND29: C59.2, C60.2, J88.1, J89.1, R175.1, R178.1, TP117.1, U30.8, U30.9
GND30: C61.2, C62.2, J91.1, J92.1, R181.1, R184.1, TP121.1, U31.8, U31.9
GND31: C63.2, C64.2, J94.1, J95.1, R187.1, R190.1, TP125.1, U32.8, U32.9
GND32: C65.2, C66.2, J97.1, J98.1, R193.1, R196.1, TP129.1, U33.8, U33.9
GND33: C67.2, C68.2, J100.1, J101.1, R199.1, R202.1, TP133.1, U34.8, U34.9
GND34: C69.2, C70.2, J103.1, J104.1, R205.1, R208.1, TP137.1, U35.8, U35.9
GND35: C71.2, C72.2, J106.1, J107.1, R211.1, R214.1, TP141.1, U36.8, U36.9
GND36: C73.2, C74.2, J109.1, J110.1, R217.1, R220.1, TP145.1, U37.8, U37.9
GND37: C75.2, C76.2, J112.1, J113.1, R223.1, R226.1, TP149.1, U38.8, U38.9
GND38: C77.2, C78.2, J115.1, J116.1, R229.1, R232.1, TP153.1, U39.8, U39.9
GND39: C79.2, C80.2, J118.1, J119.1, R235.1, R238.1, TP157.1, U40.8, U40.9
GND40: C81.2, C82.2, J121.1, J122.1, R241.1, R244.1, TP161.1, U41.8, U41.9
GND41: C83.2, C84.2, J124.1, J125.1, R247.1, R250.1, TP165.1, U42.8, U42.9
GND42: C85.2, C86.2, J127.1, J128.1, R253.1, R256.1, TP169.1, U43.8, U43.9
GND43: C87.2, C88.2, J130.1, J131.1, R259.1, R262.1, TP173.1, U44.8, U44.9
GND44: C89.2, C90.2, J133.1, J134.1, R265.1, R268.1, TP177.1, U45.8, U45.9
GND45: C91.2, C92.2, J136.1, J137.1, R271.1, R274.1, TP181.1, U46.8, U46.9
GND46: C93.2, C94.2, J139.1, J140.1, R277.1, R280.1, TP185.1, U47.8, U47.9
GND47: C95.2, C96.2, J142.1, J143.1, R283.1, R286.1, TP189.1, U48.8, U48.9
GND48: C97.2, C98.2, J145.1, J146.1, R289.1, R292.1, TP193.1, U49.8, U49.9
GND49: C99.2, C100.2, J148.1, J149.1, R295.1, R298.1, TP197.1, U50.8, U50.9
GND50: C101.2, C102.2, J151.1, J152.1, R301.1, R304.1, TP201.1, U51.8, U51.9
GND51: C103.2, C104.2, J154.1, J155.1, R307.1, R310.1, TP205.1, U52.8, U52.9
GND52: C105.2, C106.2, J157.1, J158.1, R313.1, R316.1, TP209.1, U53.8, U53.9
GND53: C107.2, C108.2, J160.1, J161.1, R319.1, R322.1, TP213.1, U54.8, U54.9
GND54: C109.2, C110.2, J163.1, J164.1, R325.1, R328.1, TP217.1, U55.8, U55.9
GND55: C111.2, C112.2, J166.1, J167.1, R331.1, R334.1, TP221.1, U56.8, U56.9
GND56: C113.2, C114.2, J169.1, J170.1, R337.1, R340.1, TP225.1, U57.8, U57.9
GND57: C115.2, C116.2, J172.1, J173.1, R343.1, R346.1, TP229.1, U58.8, U58.9
GND58: C117.2, C118.2, J175.1, J176.1, R349.1, R352.1, TP233.1, U59.8, U59.9
GND59: C119.2, C120.2, J178.1, J179.1, R355.1, R358.1, TP237.1, U60.8, U60.9
GND60: C121.2, C122.2, J181.1, J182.1, R361.1, R364.1, TP241.1, U61.8, U61.9
GND61: C123.2, C124.2, J184.1, J185.1, R367.1, R370.1, TP245.1, U62.8, U62.9
GND62: C125.2, C126.2, J187.1, J188.1, R373.1, R376.1, TP249.1, U63.8, U63.9
GND63: C127.2, C128.2, J190.1, J191.1, R379.1, R382.1, TP253.1, U64.8, U64.9
INT1: J3.1, U1.5
INT3: J6.1, U2.5
INT5: J9.1, U3.5
INT7: J12.1, U4.5
INT9: J15.1, U5.5
INT11: J18.1, U6.5
INT13: J21.1, U7.5
INT15: J24.1, U8.5
INT17: J27.1, U9.5
INT19: J30.1, U10.5
INT21: J33.1, U11.5
INT23: J36.1, U12.5
INT25: J39.1, U13.5
INT27: J42.1, U14.5
INT29: J45.1, U15.5
INT31: J48.1, U16.5
INT33: J51.1, U17.5
INT35: J54.1, U18.5
INT37: J57.1, U19.5
INT39: J60.1, U20.5
INT41: J63.1, U21.5
INT43: J66.1, U22.5
INT45: J69.1, U23.5
INT47: J72.1, U24.5
INT49: J75.1, U25.5
INT51: J78.1, U26.5
INT53: J81.1, U27.5
INT55: J84.1, U28.5
INT57: J87.1, U29.5
INT59: J90.1, U30.5
INT61: J93.1, U31.5
INT63: J96.1, U32.5
INT65: J99.1, U33.5
INT67: J102.1, U34.5
INT69: J105.1, U35.5
INT71: J108.1, U36.5
INT73: J111.1, U37.5
INT75: J114.1, U38.5
INT77: J117.1, U39.5
INT79: J120.1, U40.5
INT81: J123.1, U41.5
INT83: J126.1, U42.5
INT85: J129.1, U43.5
INT87: J132.1, U44.5
INT89: J135.1, U45.5
INT91: J138.1, U46.5
INT93: J141.1, U47.5
INT95: J144.1, U48.5
INT97: J147.1, U49.5
INT99: J150.1, U50.5
INT101: J153.1, U51.5
INT103: J156.1, U52.5
INT105: J159.1, U53.5
INT107: J162.1, U54.5
INT109: J165.1, U55.5
INT111: J168.1, U56.5
INT113: J171.1, U57.5
INT115: J174.1, U58.5
INT117: J177.1, U59.5
INT119: J180.1, U60.5
INT121: J183.1, U61.5
INT123: J186.1, U62.5
INT125: J189.1, U63.5
INT127: J192.1, U64.5
unnamed: D1.A, PWR.1
unnamed: D1.C, R1.2
unnamed: I2C.3, R2.2
unnamed: I2C.1, R3.1
unnamed: ADR.1, R5.1
unnamed: ADR.3, R4.2
unnamed: D2.C, R7.2
unnamed: I2C1.3, R8.2
unnamed: I2C1.1, R9.1
unnamed: ADR1.1, R11.1
unnamed: ADR1.3, R10.2
unnamed: D2.A, PWR1.1
unnamed: D3.C, R13.2
unnamed: I2C2.3, R14.2
unnamed: I2C2.1, R15.1
unnamed: ADR2.1, R17.1
unnamed: ADR2.3, R16.2
unnamed: D3.A, PWR2.1
unnamed: D4.C, R19.2
unnamed: I2C3.3, R20.2
unnamed: I2C3.1, R21.1
unnamed: ADR3.1, R23.1
unnamed: ADR3.3, R22.2
unnamed: D4.A, PWR3.1
unnamed: D5.C, R25.2
unnamed: I2C4.3, R26.2
unnamed: I2C4.1, R27.1
unnamed: ADR4.1, R29.1
unnamed: ADR4.3, R28.2
unnamed: D5.A, PWR4.1
unnamed: D6.C, R31.2
unnamed: I2C5.3, R32.2
unnamed: I2C5.1, R33.1
unnamed: ADR5.1, R35.1
unnamed: ADR5.3, R34.2
unnamed: D6.A, PWR5.1
unnamed: D7.C, R37.2
unnamed: I2C6.3, R38.2
unnamed: I2C6.1, R39.1
unnamed: ADR6.1, R41.1
unnamed: ADR6.3, R40.2
unnamed: D7.A, PWR6.1
unnamed: D8.C, R43.2
unnamed: I2C7.3, R44.2
unnamed: I2C7.1, R45.1
unnamed: ADR7.1, R47.1
unnamed: ADR7.3, R46.2
unnamed: D8.A, PWR7.1
unnamed: D9.C, R49.2
unnamed: I2C8.3, R50.2
unnamed: I2C8.1, R51.1
unnamed: ADR8.1, R53.1
unnamed: ADR8.3, R52.2
unnamed: D9.A, PWR8.1
unnamed: D10.C, R55.2
unnamed: I2C9.3, R56.2
unnamed: I2C9.1, R57.1
unnamed: ADR9.1, R59.1
unnamed: ADR9.3, R58.2
unnamed: D10.A, PWR9.1
unnamed: D11.C, R61.2
unnamed: I2C10.3, R62.2
unnamed: I2C10.1, R63.1
unnamed: ADR10.1, R65.1
unnamed: ADR10.3, R64.2
unnamed: D11.A, PWR10.1
unnamed: D12.C, R67.2
unnamed: I2C11.3, R68.2
unnamed: I2C11.1, R69.1
unnamed: ADR11.1, R71.1
unnamed: ADR11.3, R70.2
unnamed: D12.A, PWR11.1
unnamed: D13.C, R73.2
unnamed: I2C12.3, R74.2
unnamed: I2C12.1, R75.1
unnamed: ADR12.1, R77.1
unnamed: ADR12.3, R76.2
unnamed: D13.A, PWR12.1
unnamed: D14.C, R79.2
unnamed: I2C13.3, R80.2
unnamed: I2C13.1, R81.1
unnamed: ADR13.1, R83.1
unnamed: ADR13.3, R82.2
unnamed: D14.A, PWR13.1
unnamed: D15.C, R85.2
unnamed: I2C14.3, R86.2
unnamed: I2C14.1, R87.1
unnamed: ADR14.1, R89.1
unnamed: ADR14.3, R88.2
unnamed: D15.A, PWR14.1
unnamed: D16.C, R91.2
unnamed: I2C15.3, R92.2
unnamed: I2C15.1, R93.1
unnamed: ADR15.1, R95.1
unnamed: ADR15.3, R94.2
unnamed: D16.A, PWR15.1
unnamed: D17.C, R97.2
unnamed: I2C16.3, R98.2
unnamed: I2C16.1, R99.1
unnamed: ADR16.1, R101.1
unnamed: ADR16.3, R100.2
unnamed: D17.A, PWR16.1
unnamed: D18.C, R103.2
unnamed: I2C17.3, R104.2
unnamed: I2C17.1, R105.1
unnamed: ADR17.1, R107.1
unnamed: ADR17.3, R106.2
unnamed: D18.A, PWR17.1
unnamed: D19.C, R109.2
unnamed: I2C18.3, R110.2
unnamed: I2C18.1, R111.1
unnamed: ADR18.1, R113.1
unnamed: ADR18.3, R112.2
unnamed: D19.A, PWR18.1
unnamed: D20.C, R115.2
unnamed: I2C19.3, R116.2
unnamed: I2C19.1, R117.1
unnamed: ADR19.1, R119.1
unnamed: ADR19.3, R118.2
unnamed: D20.A, PWR19.1
unnamed: D21.C, R121.2
unnamed: I2C20.3, R122.2
unnamed: I2C20.1, R123.1
unnamed: ADR20.1, R125.1
unnamed: ADR20.3, R124.2
unnamed: D21.A, PWR20.1
unnamed: D22.C, R127.2
unnamed: I2C21.3, R128.2
unnamed: I2C21.1, R129.1
unnamed: ADR21.1, R131.1
unnamed: ADR21.3, R130.2
unnamed: D22.A, PWR21.1
unnamed: D23.C, R133.2
unnamed: I2C22.3, R134.2
unnamed: I2C22.1, R135.1
unnamed: ADR22.1, R137.1
unnamed: ADR22.3, R136.2
unnamed: D23.A, PWR22.1
unnamed: D24.C, R139.2
unnamed: I2C23.3, R140.2
unnamed: I2C23.1, R141.1
unnamed: ADR23.1, R143.1
unnamed: ADR23.3, R142.2
unnamed: D24.A, PWR23.1
unnamed: D25.C, R145.2
unnamed: I2C24.3, R146.2
unnamed: I2C24.1, R147.1
unnamed: ADR24.1, R149.1
unnamed: ADR24.3, R148.2
unnamed: D25.A, PWR24.1
unnamed: D26.C, R151.2
unnamed: I2C25.3, R152.2
unnamed: I2C25.1, R153.1
unnamed: ADR25.1, R155.1
unnamed: ADR25.3, R154.2
unnamed: D26.A, PWR25.1
unnamed: D27.C, R157.2
unnamed: I2C26.3, R158.2
unnamed: I2C26.1, R159.1
unnamed: ADR26.1, R161.1
unnamed: ADR26.3, R160.2
unnamed: D27.A, PWR26.1
unnamed: D28.C, R163.2
unnamed: I2C27.3, R164.2
unnamed: I2C27.1, R165.1
unnamed: ADR27.1, R167.1
unnamed: ADR27.3, R166.2
unnamed: D28.A, PWR27.1
unnamed: D29.C, R169.2
unnamed: I2C28.3, R170.2
unnamed: I2C28.1, R171.1
unnamed: ADR28.1, R173.1
unnamed: ADR28.3, R172.2
unnamed: D29.A, PWR28.1
unnamed: D30.C, R175.2
unnamed: I2C29.3, R176.2
unnamed: I2C29.1, R177.1
unnamed: ADR29.1, R179.1
unnamed: ADR29.3, R178.2
unnamed: D30.A, PWR29.1
unnamed: D31.C, R181.2
unnamed: I2C30.3, R182.2
unnamed: I2C30.1, R183.1
unnamed: ADR30.1, R185.1
unnamed: ADR30.3, R184.2
unnamed: D31.A, PWR30.1
unnamed: D32.C, R187.2
unnamed: I2C31.3, R188.2
unnamed: I2C31.1, R189.1
unnamed: ADR31.1, R191.1
unnamed: ADR31.3, R190.2
unnamed: D32.A, PWR31.1
unnamed: D33.C, R193.2
unnamed: I2C32.3, R194.2
unnamed: I2C32.1, R195.1
unnamed: ADR32.1, R197.1
unnamed: ADR32.3, R196.2
unnamed: D33.A, PWR32.1
unnamed: D34.C, R199.2
unnamed: I2C33.3, R200.2
unnamed: I2C33.1, R201.1
unnamed: ADR33.1, R203.1
unnamed: ADR33.3, R202.2
unnamed: D34.A, PWR33.1
unnamed: D35.C, R205.2
unnamed: I2C34.3, R206.2
unnamed: I2C34.1, R207.1
unnamed: ADR34.1, R209.1
unnamed: ADR34.3, R208.2
unnamed: D35.A, PWR34.1
unnamed: D36.C, R211.2
unnamed: I2C35.3, R212.2
unnamed: I2C35.1, R213.1
unnamed: ADR35.1, R215.1
unnamed: ADR35.3, R214.2
unnamed: D36.A, PWR35.1
unnamed: D37.C, R217.2
unnamed: I2C36.3, R218.2
unnamed: I2C36.1, R219.1
unnamed: ADR36.1, R221.1
unnamed: ADR36.3, R220.2
unnamed: D37.A, PWR36.1
unnamed: D38.C, R223.2
unnamed: I2C37.3, R224.2
unnamed: I2C37.1, R225.1
unnamed: ADR37.1, R227.1
unnamed: ADR37.3, R226.2
unnamed: D38.A, PWR37.1
unnamed: D39.C, R229.2
unnamed: I2C38.3, R230.2
unnamed: I2C38.1, R231.1
unnamed: ADR38.1, R233.1
unnamed: ADR38.3, R232.2
unnamed: D39.A, PWR38.1
unnamed: D40.C, R235.2
unnamed: I2C39.3, R236.2
unnamed: I2C39.1, R237.1
unnamed: ADR39.1, R239.1
unnamed: ADR39.3, R238.2
unnamed: D40.A, PWR39.1
unnamed: D41.C, R241.2
unnamed: I2C40.3, R242.2
unnamed: I2C40.1, R243.1
unnamed: ADR40.1, R245.1
unnamed: ADR40.3, R244.2
unnamed: D41.A, PWR40.1
unnamed: D42.C, R247.2
unnamed: I2C41.3, R248.2
unnamed: I2C41.1, R249.1
unnamed: ADR41.1, R251.1
unnamed: ADR41.3, R250.2
unnamed: D42.A, PWR41.1
unnamed: D43.C, R253.2
unnamed: I2C42.3, R254.2
unnamed: I2C42.1, R255.1
unnamed: ADR42.1, R257.1
unnamed: ADR42.3, R256.2
unnamed: D43.A, PWR42.1
unnamed: D44.C, R259.2
unnamed: I2C43.3, R260.2
unnamed: I2C43.1, R261.1
unnamed: ADR43.1, R263.1
unnamed: ADR43.3, R262.2
unnamed: D44.A, PWR43.1
unnamed: D45.C, R265.2
unnamed: I2C44.3, R266.2
unnamed: I2C44.1, R267.1
unnamed: ADR44.1, R269.1
unnamed: ADR44.3, R268.2
unnamed: D45.A, PWR44.1
unnamed: D46.C, R271.2
unnamed: I2C45.3, R272.2
unnamed: I2C45.1, R273.1
unnamed: ADR45.1, R275.1
unnamed: ADR45.3, R274.2
unnamed: D46.A, PWR45.1
unnamed: D47.C, R277.2
unnamed: I2C46.3, R278.2
unnamed: I2C46.1, R279.1
unnamed: ADR46.1, R281.1
unnamed: ADR46.3, R280.2
unnamed: D47.A, PWR46.1
unnamed: D48.C, R283.2
unnamed: I2C47.3, R284.2
unnamed: I2C47.1, R285.1
unnamed: ADR47.1, R287.1
unnamed: ADR47.3, R286.2
unnamed: D48.A, PWR47.1
unnamed: D49.C, R289.2
unnamed: I2C48.3, R290.2
unnamed: I2C48.1, R291.1
unnamed: ADR48.1, R293.1
unnamed: ADR48.3, R292.2
unnamed: D49.A, PWR48.1
unnamed: D50.C, R295.2
unnamed: I2C49.3, R296.2
unnamed: I2C49.1, R297.1
unnamed: ADR49.1, R299.1
unnamed: ADR49.3, R298.2
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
